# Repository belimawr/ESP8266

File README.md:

ESP8266 - Breakoutboard
=======================

A small breakout board for the ESP8266.
This board was developed for uploading new firmwares (e.g. Micropython) and prototyping.

Licence
-------
Copyright 2016 Tiago Queiroz

<br />
This work is licensed under a <a rel="license" href="http://creativecommons.org/licenses/by/4.0/">Creative Commons Attribution 4.0 International License</a>.

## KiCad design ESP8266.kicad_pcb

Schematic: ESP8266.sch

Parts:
C1: 100nF; C_Radial_D6.3_L11.2_P2.5
C2: 10uf; C_Radial_D5_L6_P2.5
K1: USB/Serial; Pin_Header_Straight_1x03
P1: CONN_01X07; Pin_Header_Straight_1x07
P2: CONN_01X02; Pin_Header_Straight_1x02
P3: CONN_01X06; Pin_Header_Straight_1x06
P4: CONN_01X03; bornier3
R1, R2, R3: 10k; R3
SW2: SW_PUSH; SW_PUSH_SMALL
U1: NCP1117ST33T3G; TO-220_Neutral123_Vertical
U2: ESP-07v2; ESP-12

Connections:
+3V3: C2.1, P4.2, R1.1, R2.1, R3.1, U1.2, U2.8
GND: C1.2, C2.2, K1.1, P1.7, P2.1, P4.1, SW2.2, U1.1, U2.9, U2.10
unnamed: K1.2, P1.2, U2.15
unnamed: K1.3, P1.1, U2.16
unnamed: P1.3, U2.14
unnamed: P1.4, U2.13
unnamed: P1.5, P2.2, U2.12
unnamed: P1.6, R1.2, U2.11
unnamed: P3.1, U2.7
unnamed: P3.2, U2.6
unnamed: P3.3, U2.5
unnamed: P3.4, U2.4
unnamed: P3.5, R2.2, U2.3
unnamed: P3.6, U2.2
unnamed: R3.2, SW2.1, U2.1
VCC: C1.1, P4.3, U1.3

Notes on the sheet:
5V até 12V

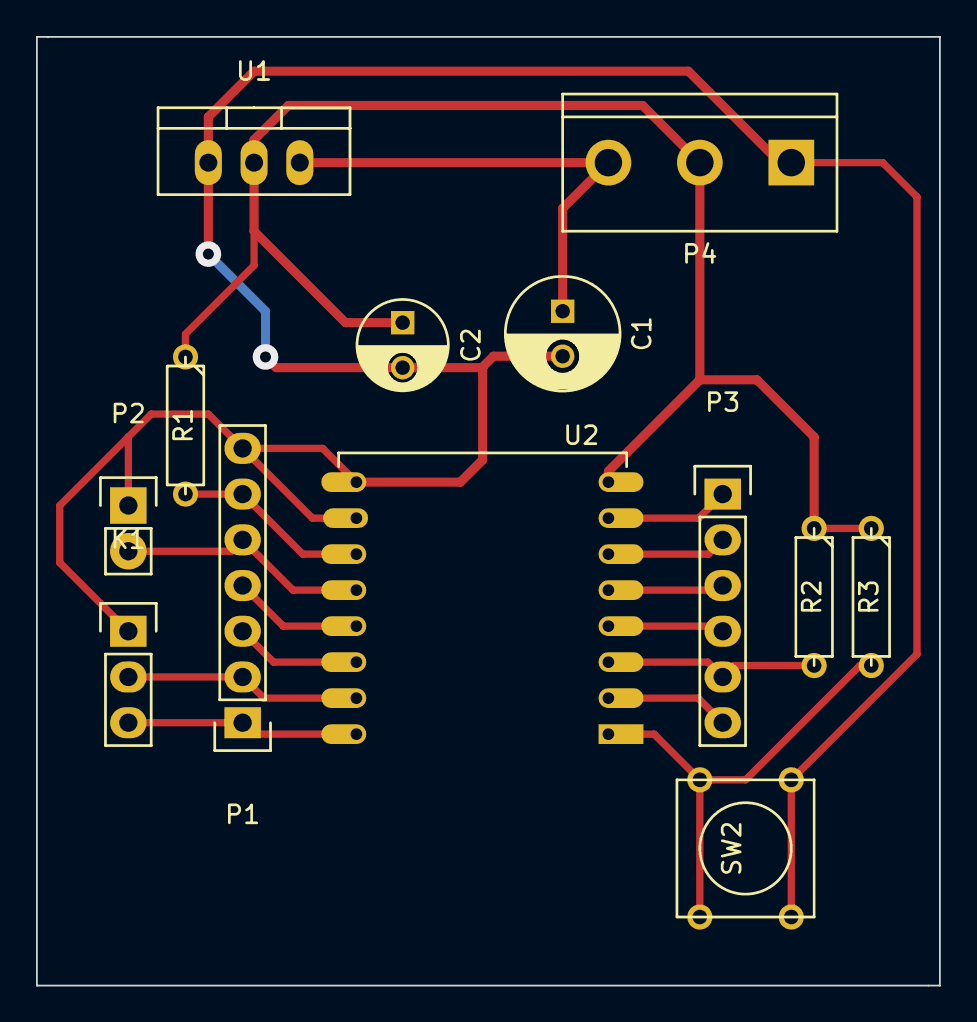
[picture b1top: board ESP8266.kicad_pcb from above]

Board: 2 copper layers, 50.2 x 52.7 mm, 13 parts (0 on the bottom side), 16 nets.

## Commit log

2016-07-02 Init. V0.1
2016-07-02 Adding Schematic in PDF
